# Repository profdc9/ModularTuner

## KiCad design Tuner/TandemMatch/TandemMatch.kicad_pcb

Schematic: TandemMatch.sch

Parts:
C1, C2, C3, C4, C5, C6, C7, C8: 10 nF; C_Disc_D5.0mm_W2.5mm_P5.00mm
C12: 10 nF; C_Disc_D5.0mm_W2.5mm_P2.50mm
D1, D2: 1N5711; D_DO-35_SOD27_P7.62mm_Horizontal
D3: D_Zener; D_DO-41_SOD81_P10.16mm_Horizontal
D4, D5: 1N4004; D_DO-41_SOD81_P10.16mm_Horizontal
D7, D8: 1N4148; D_DO-35_SOD27_P7.62mm_Horizontal
F1: Keystone 3544-2 / SL-506P; SL506Pfuseholder
J1, J2, J19: Conn_01x02; TerminalBlock_bornier-2_P5.08mm
J3, J4, J18, J20: Conn_Coaxial; bnc_90_1-1337543-0_pad_combo
J5, J6, J7, J8, J9, J10, J11, J12, J13, J14, J15, J16, J21, J22, J23, J24, J25, J26, J27, J28, J29, J30, J31, J32: Conn_01x01; 1pin
J17: Barrel_Jack; BARREL_JACK
J33: Conn_01x03; Pin_Header_Straight_1x03_Pitch2.54mm
JP1, JP2, JP3, JP4, JP5, JP6, JP7, JP8, JP9, JP12: Jumper_NC_Small; Pin_Header_Straight_1x02_Pitch2.54mm
L1: L; BigRFChokeInductor
R1, R2, R3, R4: 100R; R_Axial_DIN0309_L9.0mm_D3.2mm_P12.70mm_Horizontal
R5, R6, R7, R8, R21: 10k; R_Axial_DIN0207_L6.3mm_D2.5mm_P7.62mm_Horizontal
R23: 1k; R_Axial_DIN0207_L6.3mm_D2.5mm_P7.62mm_Horizontal

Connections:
GND: C1.2, C2.2, C3.2, C4.2, C7.2, C8.2, C12.2, D4.2 (A), D5.1 (K), J1.2, J2.2, J3.2 (Ext), J4.2 (Ext), J5.1, J6.1, J15.1, J16.1, J17.2, J18.2 (Ext), J19.2, J20.2 (Ext), J21.1, J22.1, J23.1, J24.1, J25.1, J26.1, J27.1, J28.1, J29.1, J32.1, J33.3, JP4.1, R1.1, R2.1, R3.1, R4.1, R6.1, R8.1, R23.1
unnamed: C1.1, D1.1 (K), R5.2
unnamed: C2.1, J33.1, R5.1, R6.2
unnamed: C3.1, D2.1 (K), R7.2
unnamed: C4.1, J33.2, R7.1, R8.2
unnamed: C5.1, C6.1, J13.1
unnamed: C5.2, C6.2, J20.1 (In), L1.2
unnamed: C7.1, C8.1, D3.1, D4.1 (K), F1.1, J1.1, J2.1, J17.1, J19.1, JP1.1
unnamed: C12.1, JP4.2, R21.1, R23.2
unnamed: D1.2 (A), JP9.1
unnamed: D2.2 (A), JP12.1
unnamed: D3.2, D5.2 (A)
unnamed: D7.1 (K), D8.2 (A)
unnamed: D7.2 (A), JP3.2
unnamed: D8.1 (K), R21.2
unnamed: F1.2, JP1.2, JP2.1
unnamed: J3.1 (In), JP7.2
unnamed: J7.1, JP5.2, JP7.1, JP9.2
unnamed: J11.1, J31.1, JP6.2, JP8.2, JP12.2
unnamed: J18.1 (In), JP8.1
unnamed: J4.1 (In), J9.1, J30.1, JP3.1
unnamed: JP2.2, L1.1
unnamed: JP5.1, R1.2, R2.2
unnamed: JP6.1, R3.2, R4.2

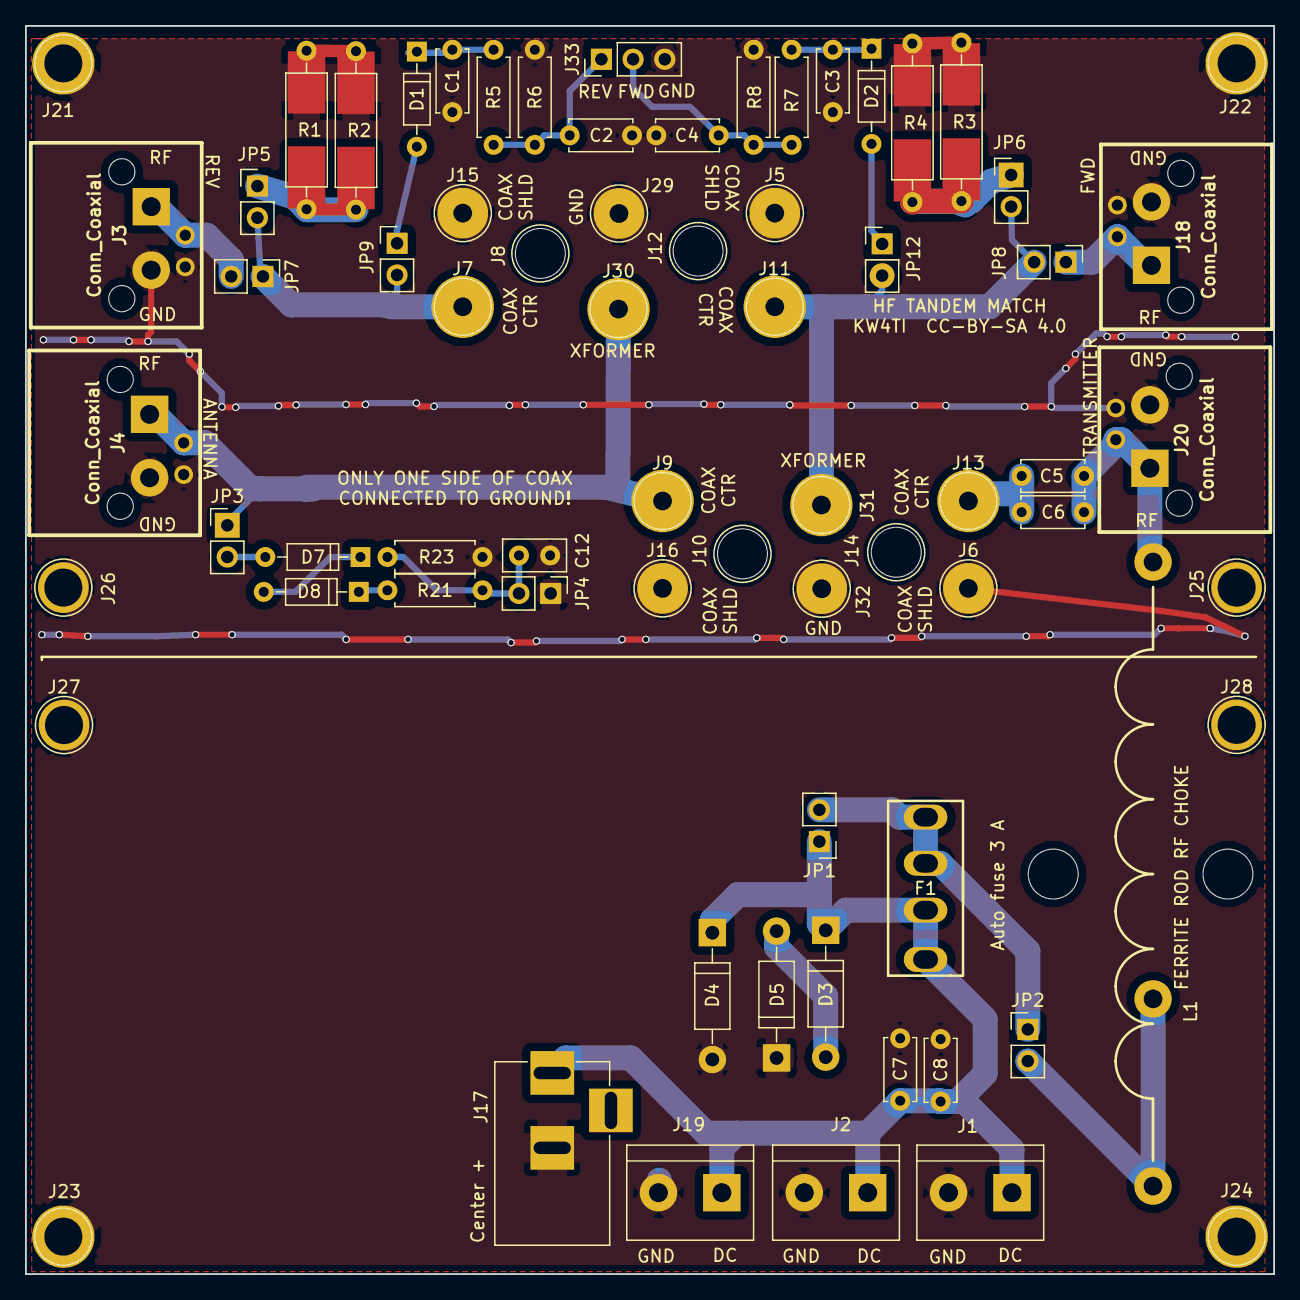
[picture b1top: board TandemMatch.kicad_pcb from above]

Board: 2 copper layers, 100.0 x 100.0 mm, 71 parts (0 on the bottom side), 24 nets.

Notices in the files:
Tuner/TandemMatch/TandemMatch.kicad_pcb:
KW4TI  CC-BY-SA 4.0
